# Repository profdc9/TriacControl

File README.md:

# TriacControl

This is an optoisolated triac motor speed controller where the phase control of the motor AC signal may be controlled by an analog or PWM signal.
Typically, a universal motor tool such as a drill or a router could have it's speed varied this way.
A PWM signal would usually be supplied by a microcontroller.  This motor speed control is open-loop and you have to add a tachometer
if you want to be able to vary the motor speed to achieve a particular rotation rate.

The voltage for the control may be 3.3 v, 5v, or up to 24 v.  A resistor (one of R17,R18,R19) and a capacitor (one of C2,C3,C4) determine how
the voltage/PWM signal varies the motor speed control.  The minimum control voltage to turn on the triac is about 1.75 V.  3.3V control uses
a 100 ohm resistor and a 22 uF capacitor, a 5 V control uses a 470 ohm resistor and a 47 uF capacitor, 12 volts uses a 2k2 resistor and 47 uF
capacitor, and 24 V uses a 4k7 resistor an 47 uF capacitor.  You may have to experiment to get it to put the control voltage into the required
range.  If you have an incandescent light bulb, you can use that as the load rather than the motor to see how bright it gets as you vary the
control voltage.  Three resistors and three capacitors may be placed on the board and selected using jumpers so that soldering need not be performed
to try different values.

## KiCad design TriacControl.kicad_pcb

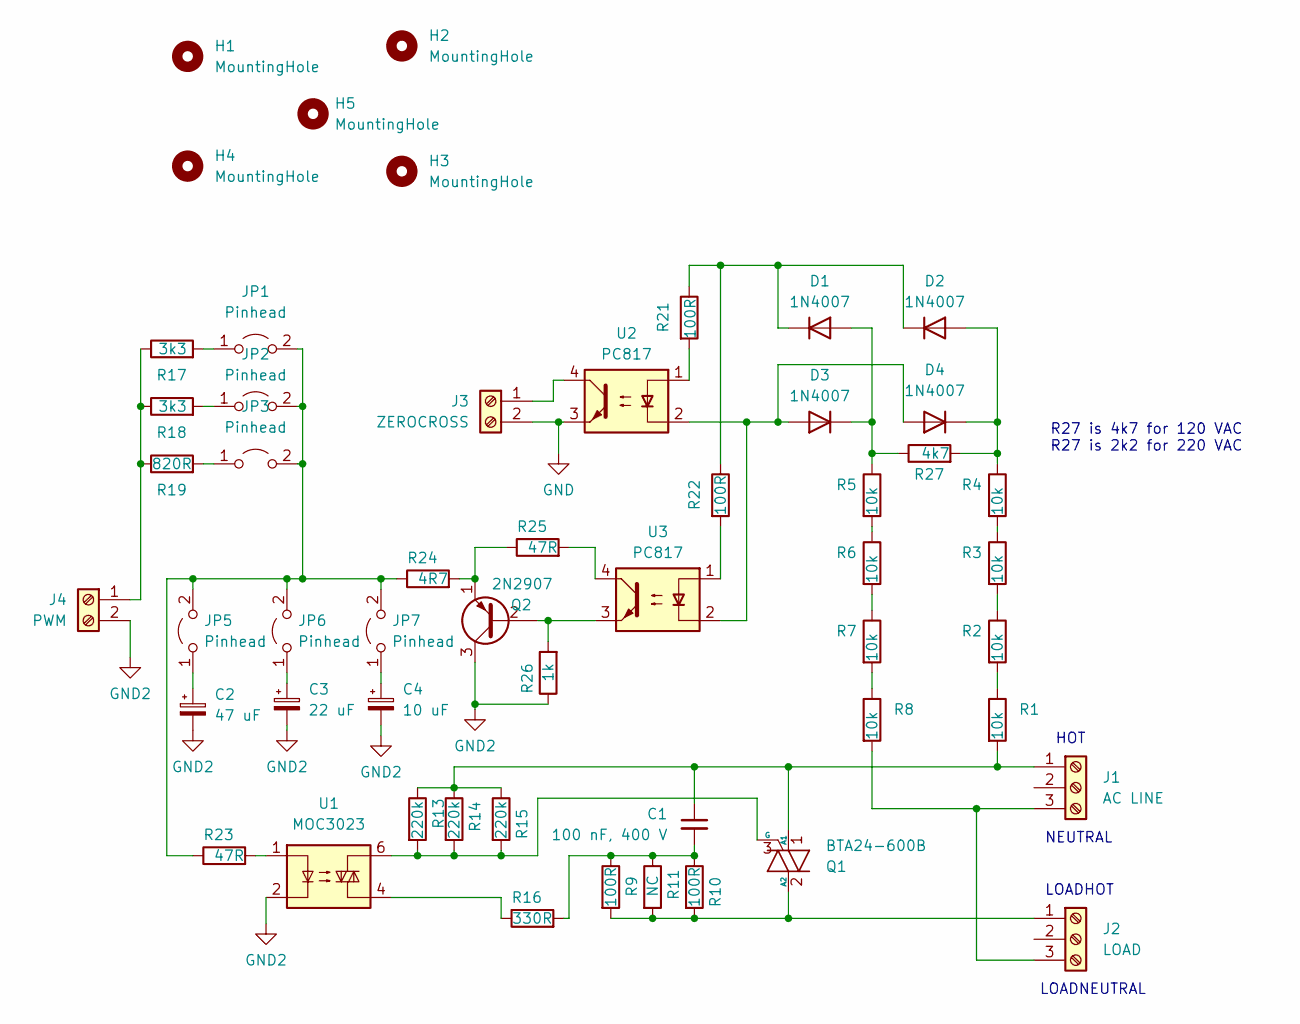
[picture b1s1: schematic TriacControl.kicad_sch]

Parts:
C1: 100 nF, 400 V; C_Rect_L10.0mm_W2.5mm_P7.50mm_MKS4
C2: 47 uF; CP_Radial_D5.0mm_P2.50mm
C3: 22 uF; CP_Radial_D5.0mm_P2.50mm
C4: 10 uF; CP_Radial_D5.0mm_P2.50mm
D1, D2, D3, D4: 1N4007; D_DO-41_SOD81_P7.62mm_Horizontal
H1, H2, H3, H4: MountingHole; MountingHole_3.2mm_M3
H5: MountingHole; MountingHole_2.1mm
J1: AC LINE; TerminalBlock_bornier-3_P5.08mm
J2: LOAD; TerminalBlock_bornier-3_P5.08mm
J3: ZEROCROSS; TerminalBlock_bornier-2_P5.08mm
J4: PWM; TerminalBlock_bornier-2_P5.08mm
JP1, JP2, JP3, JP5, JP6, JP7: Pinhead; PinHeader_1x02_P2.54mm_Vertical
Q1: BTA24-600B; TO-220-3_Vertical
Q2: 2N2907; TO-92_Inline_Wide
R1, R2, R3, R4, R5, R6, R7, R8: 10k; R_Axial_DIN0207_L6.3mm_D2.5mm_P7.62mm_Horizontal
R9, R10, R21, R22: 100R; R_Axial_DIN0207_L6.3mm_D2.5mm_P7.62mm_Horizontal
R11: NC; R_Axial_DIN0207_L6.3mm_D2.5mm_P7.62mm_Horizontal
R13, R14, R15: 220k; R_Axial_DIN0207_L6.3mm_D2.5mm_P7.62mm_Horizontal
R16: 330R; R_Axial_DIN0207_L6.3mm_D2.5mm_P7.62mm_Horizontal
R17, R18: 3k3; R_Axial_DIN0309_L9.0mm_D3.2mm_P15.24mm_Horizontal
R19: 820R; R_Axial_DIN0309_L9.0mm_D3.2mm_P15.24mm_Horizontal
R23, R25: 47R; R_Axial_DIN0207_L6.3mm_D2.5mm_P7.62mm_Horizontal
R24: 4R7; R_Axial_DIN0207_L6.3mm_D2.5mm_P7.62mm_Horizontal
R26: 1k; R_Axial_DIN0207_L6.3mm_D2.5mm_P7.62mm_Horizontal
R27: 4k7; R_Axial_DIN0207_L6.3mm_D2.5mm_P7.62mm_Horizontal
U1: MOC3023; DIP-6_W7.62mm_Socket
U2, U3: PC817; DIP-4_W7.62mm

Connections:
GND: J3.2, U2.3
GND2: C2.2, C3.2, C4.2, J4.2, Q2.3 (C), R26.1, U1.2
unnamed: C1.2, R9.1, R10.1, R11.1, R16.2
unnamed: D1.2 (A), D3.1 (K), R5.1, R27.1
unnamed: D1.1 (K), D2.1 (K), R21.1, R22.1
unnamed: D2.2 (A), D4.1 (K), R4.1, R27.2
unnamed: D3.2 (A), D4.2 (A), U2.2, U3.2
unnamed: C1.1, J1.1, Q1.1 (A1), R1.2, R13.1, R14.1, R15.1
unnamed: J1.3, J2.3, R8.2
unnamed: J2.1, Q1.2 (A2), R9.2, R10.2, R11.2
unnamed: J3.1, U2.4
unnamed: J4.1, R17.1, R18.1, R19.1
unnamed: JP1.1 (A), R17.2
unnamed: JP1.2 (B), JP2.2 (B), JP3.2 (B), JP5.2 (B), JP6.2 (B), JP7.2 (B), R23.1, R24.1
unnamed: JP2.1 (A), R18.2
unnamed: JP3.1 (A), R19.2
unnamed: C2.1, JP5.1 (A)
unnamed: C3.1, JP6.1 (A)
unnamed: C4.1, JP7.1 (A)
unnamed: Q1.3 (G), R13.2, R14.2, R15.2, U1.6
unnamed: Q2.2 (B), R26.2, U3.3
unnamed: Q2.1 (E), R24.2, R25.1
unnamed: R1.1, R2.2
unnamed: R2.1, R3.2
unnamed: R3.1, R4.2
unnamed: R5.2, R6.1
unnamed: R6.2, R7.1
unnamed: R7.2, R8.1
unnamed: R16.1, U1.4
unnamed: R21.2, U2.1
unnamed: R22.2, U3.1
unnamed: R23.2, U1.1
unnamed: R25.2, U3.4

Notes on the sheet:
LOADNEUTRAL
R27 is 4k7 for 120 VAC R27 is 2k2 for 220 VAC
NEUTRAL
LOADHOT
HOT

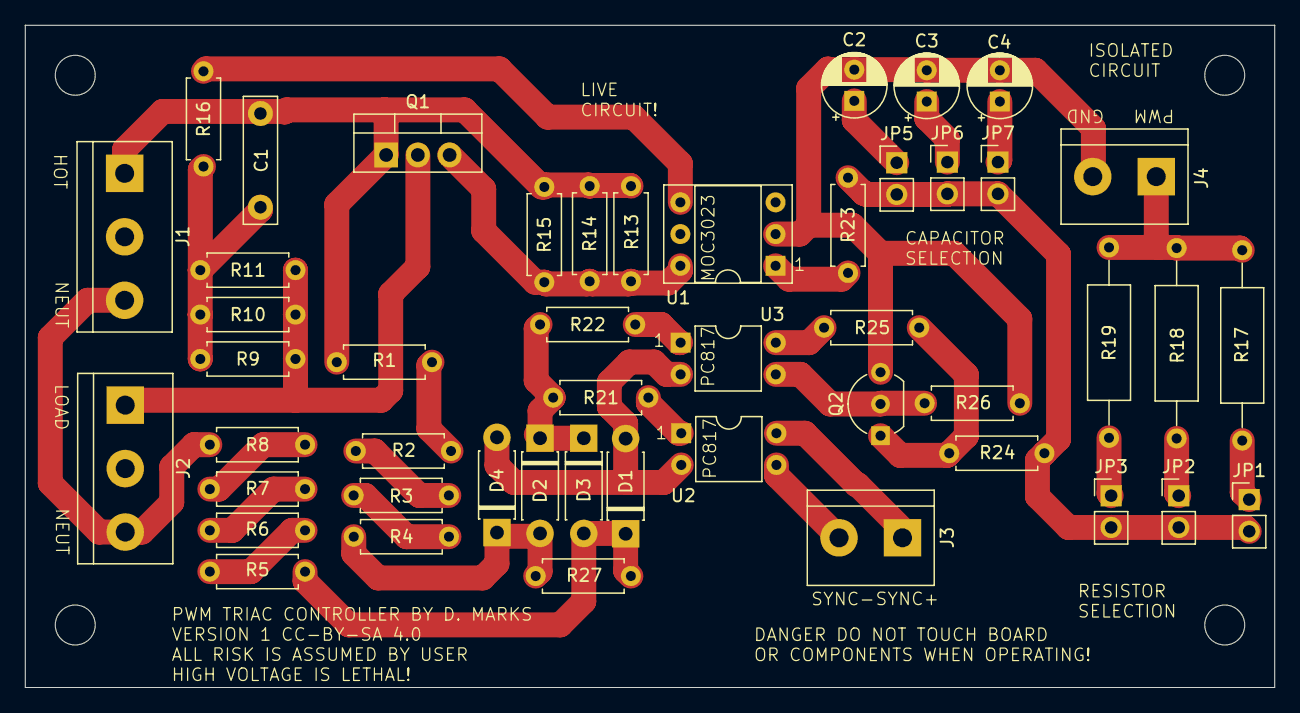
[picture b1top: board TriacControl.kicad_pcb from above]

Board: 2 copper layers, 100.0 x 53.0 mm, 53 parts (0 on the bottom side), 33 nets.

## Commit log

2025-01-28 A few changes
2025-01-29 Changed values, moved parts
2025-01-30 Fixed names and traces
2025-01-30 Changed connection to snubber, resistor size, etc.
2025-01-31 Fixed positioning of component
2025-03-11 Moved snubber capacitor
2025-03-25 Added documentation
2025-03-26 Moved components a little ore
2025-06-12 Added snubber capacitor calculation
2025-06-27 Updated TRIAC and snubber circuit

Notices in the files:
TriacControl.kicad_pcb:
VERSION 1 CC-BY-SA 4.0
